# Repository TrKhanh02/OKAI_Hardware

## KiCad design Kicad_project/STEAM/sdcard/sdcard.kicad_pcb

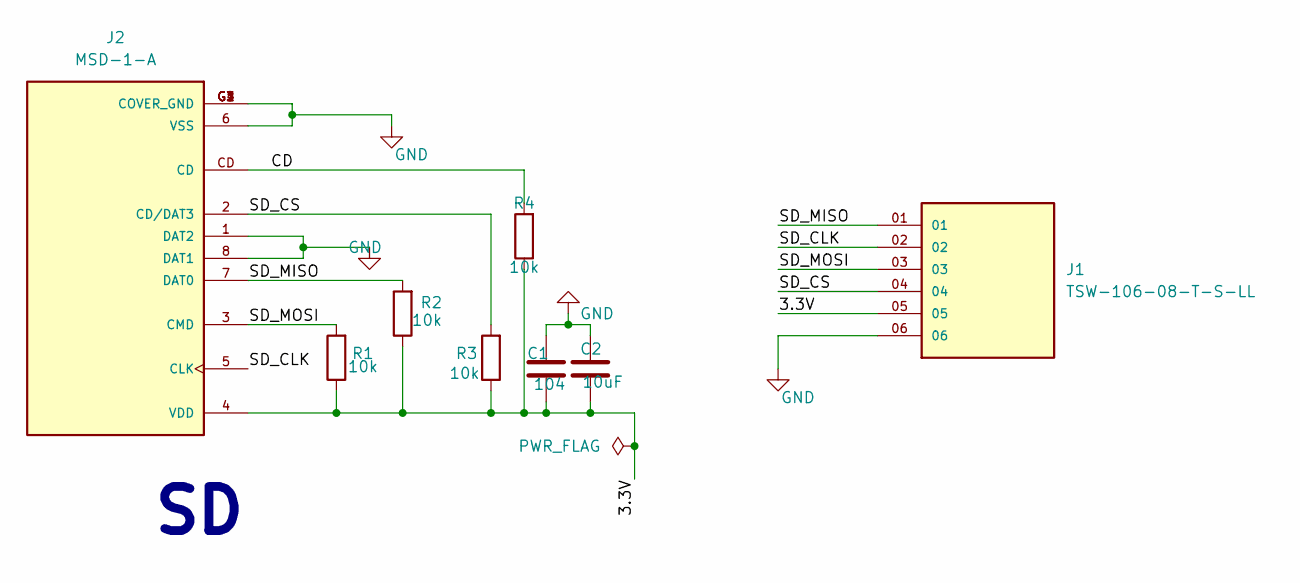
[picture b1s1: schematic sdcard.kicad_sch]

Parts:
C1: 104; C_0805_2012Metric_Pad1.18x1.45mm_HandSolder
C2: 10uF; C_0805_2012Metric_Pad1.18x1.45mm_HandSolder
J1: TSW-106-08-T-S-LL; SAMTEC_TSW-106-08-T-S-LL; PARTREV R
J2: MSD-1-A; CUI_MSD-1-A; PARTREV 1.0
R1, R2, R3, R4: 10k; R_0805_2012Metric_Pad1.20x1.40mm_HandSolder

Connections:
/3.3V: C1.1, C2.1, J1.05, J2.4 (VDD), R1.1, R2.1, R3.1, R4.1
/CD: J2.CD, R4.2
/SD_CLK: J1.02, J2.5 (CLK)
/SD_CS: J1.04, J2.2 (CD/DAT3), R3.2
/SD_MISO: J1.01, J2.7 (DAT0), R2.2
/SD_MOSI: J1.03, J2.3 (CMD), R1.2
GND: C1.2, C2.2, J1.06, J2.1 (DAT2), J2.6 (VSS), J2.8 (DAT1), J2.G1 (COVER_GND), J2.G2 (COVER_GND), J2.G3 (COVER_GND), J2.G4 (COVER_GND)

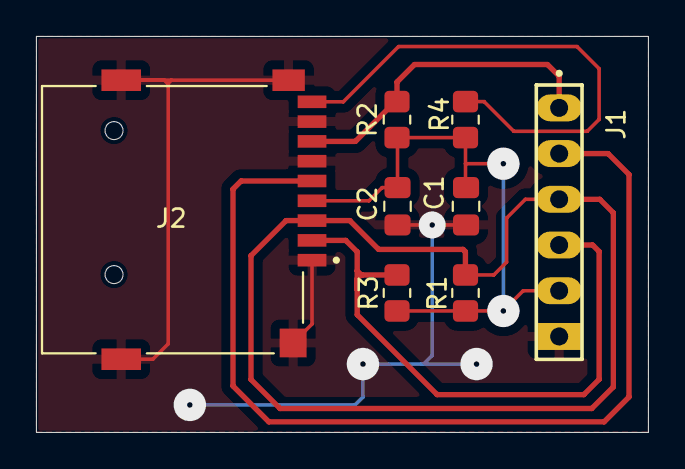
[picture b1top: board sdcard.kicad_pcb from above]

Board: 2 copper layers, 34.0 x 22.0 mm, 8 parts (0 on the bottom side), 7 nets.

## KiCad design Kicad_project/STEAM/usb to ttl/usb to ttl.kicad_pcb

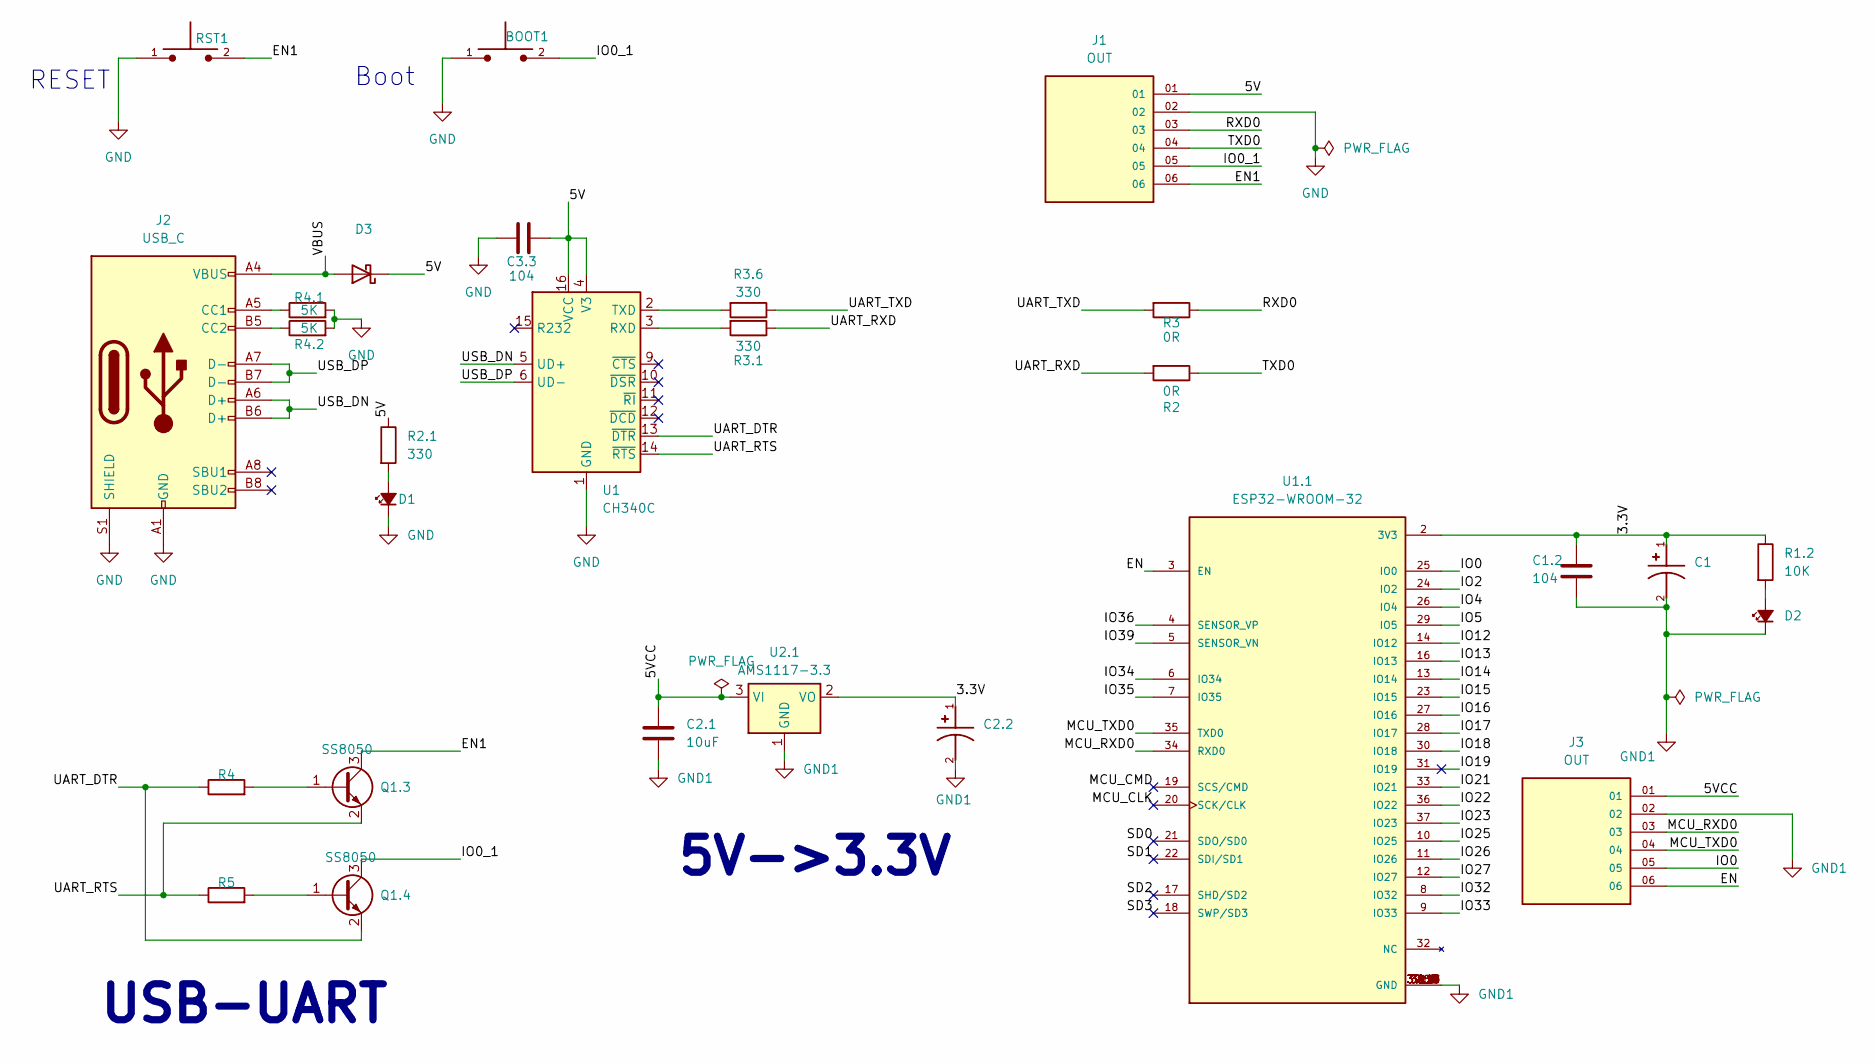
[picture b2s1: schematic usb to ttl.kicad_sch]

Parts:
BOOT1: TS10-63-26-BE-250-SMT-TR; SW_TS10-63-26-BE-250-SMT-TR; PARTREV 1.0
C1: TAJA106K016RNJ; CAPMP3216X180N; PARTREV 031320
C1.2, C3.3: 104; C_0805_2012Metric_Pad1.18x1.45mm_HandSolder
C2.1: 10uF; C_0805_2012Metric_Pad1.18x1.45mm_HandSolder
C2.2: 22uF; CAPMP3216X180N; PARTREV 031320
D1, D2: LED_Small_Filled; LED_0805_2012Metric_Pad1.15x1.40mm_HandSolder
D3: 1N5819WS; D_SOD-323_HandSoldering
J1, J3: OUT; SAMTEC_TSW-106-08-T-S-LL; PARTREV R
J2: USB_C; USB_C_Receptacle_HRO_TYPE-C-31-M-12
Q1.3, Q1.4: SS8050; SOT-23
R1.2, R4, R5: 10K; R_0805_2012Metric_Pad1.20x1.40mm_HandSolder
R2, R3: 0R; R_0805_2012Metric_Pad1.20x1.40mm_HandSolder
R2.1, R3.1, R3.6: 330; R_0805_2012Metric_Pad1.20x1.40mm_HandSolder
R4.1, R4.2: 5K; R_0805_2012Metric_Pad1.20x1.40mm_HandSolder
RST1: TS10-63-26-BE-250-SMT-TR; SW_TS10-63-26-BE-250-SMT-TR; PARTREV 1.0
U1: CH340C; SOIC-16_3.9x9.9mm_P1.27mm
U1.1: ESP32-WROOM-32; MODULE_ESP32-WROOM-32
U2.1: AMS1117-3.3; SOT-223-3_TabPin2

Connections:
/3.3V: C1.1, C1.2.1, C2.2.1, R1.2.1, U1.1.2 (3V3), U2.1.2 (VO)
/5V: C3.3.1, D3.1 (K), J1.01, R2.1.1, U1.4 (V3), U1.16 (VCC)
/5VCC: C2.1.1, J3.01, U2.1.3 (VI)
/EN: J3.06, U1.1.3 (EN)
/EN1: J1.06, Q1.3.3 (C), RST1.2
/IO0: J3.05, U1.1.25 (IO0)
/IO0_1: BOOT1.2, J1.05, Q1.4.3 (C)
/IO2: U1.1.24 (IO2)
/IO4: U1.1.26 (IO4)
/IO5: U1.1.29 (IO5)
/IO12: U1.1.14 (IO12)
/IO13: U1.1.16 (IO13)
/IO14: U1.1.13 (IO14)
/IO15: U1.1.23 (IO15)
/IO16: U1.1.27 (IO16)
/IO17: U1.1.28 (IO17)
/IO18: U1.1.30 (IO18)
/IO19: U1.1.31 (IO19)
/IO21: U1.1.33 (IO21)
/IO22: U1.1.36 (IO22)
/IO23: U1.1.37 (IO23)
/IO25: U1.1.10 (IO25)
/IO26: U1.1.11 (IO26)
/IO27: U1.1.12 (IO27)
/IO32: U1.1.8 (IO32)
/IO33: U1.1.9 (IO33)
/IO34: U1.1.6 (IO34)
/IO35: U1.1.7 (IO35)
/IO36: U1.1.4 (SENSOR_VP)
/IO39: U1.1.5 (SENSOR_VN)
/MCU_CLK: U1.1.20 (SCK/CLK)
/MCU_CMD: U1.1.19 (SCS/CMD)
/MCU_RXD0: J3.03, U1.1.34 (RXD0)
/MCU_TXD0: J3.04, U1.1.35 (TXD0)
/RXD0: J1.03, R3.1
/SD0: U1.1.21 (SDO/SD0)
/SD1: U1.1.22 (SDI/SD1)
/SD2: U1.1.17 (SHD/SD2)
/SD3: U1.1.18 (SWP/SD3)
/TXD0: J1.04, R2.1
/UART_DTR: Q1.4.2 (E), R4.1, U1.13 (~DTR)
/UART_RTS: Q1.3.2 (E), R5.1, U1.14 (~RTS)
/UART_RXD: R2.2, R3.1.1
/UART_TXD: R3.2, R3.6.1
/USB_DN: J2.A6 (D+), J2.B6 (D+), U1.5 (UD+)
/USB_DP: J2.A7 (D-), J2.B7 (D-), U1.6 (UD-)
/VBUS: D3.2 (A), J2.A4 (VBUS), J2.A9 (VBUS), J2.B4 (VBUS), J2.B9 (VBUS)
GND: BOOT1.1, C3.3.2, D1.1 (K), J1.02, J2.A1 (GND), J2.A12 (GND), J2.B1 (GND), J2.B12 (GND), J2.S1 (SHIELD), R4.1.2, R4.2.2, RST1.1, U1.1 (GND)
GND1: C1.2, C1.2.2, C2.1.2, C2.2.2, D2.1 (K), J3.02, U1.1.1 (GND), U1.1.15 (GND), U1.1.38 (GND), U1.1.39_1 (GND), U1.1.39_2 (GND), U1.1.39_3 (GND), U1.1.39_4 (GND), U1.1.39_5 (GND), U1.1.39_6 (GND), U1.1.39_7 (GND), U1.1.39_8 (GND), U1.1.39_9 (GND), U1.1.39_10 (GND), U1.1.39_11 (GND), U1.1.39_12 (GND), U1.1.39_13 (GND), U1.1.39_14 (GND), U1.1.39_15 (GND), U1.1.39_16 (GND), U1.1.39_17 (GND), U1.1.39_18 (GND), U1.1.39_19 (GND), U1.1.39_20 (GND), U1.1.39_21 (GND), U2.1.1 (GND)
unnamed: D1.2 (A), R2.1.2
unnamed: D2.2 (A), R1.2.2
unnamed: J2.A5 (CC1), R4.1.1
unnamed: J2.B5 (CC2), R4.2.1
unnamed: Q1.3.1 (B), R4.2
unnamed: Q1.4.1 (B), R5.2
unnamed: R3.1.2, U1.3 (RXD)
unnamed: R3.6.2, U1.2 (TXD)

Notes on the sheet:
USB-UART
5V->3.3V
Boot
RESET

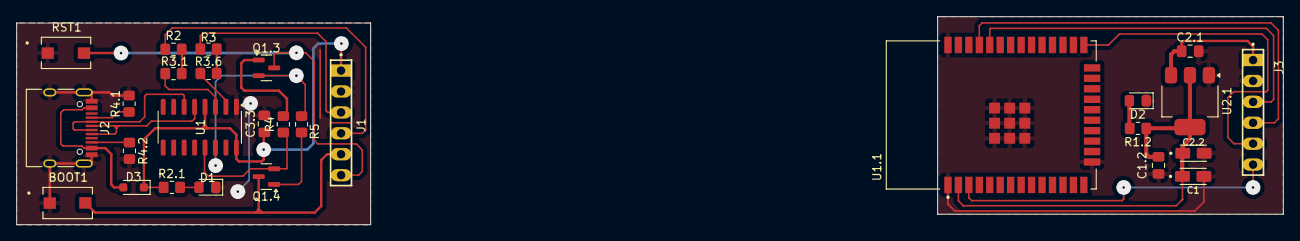
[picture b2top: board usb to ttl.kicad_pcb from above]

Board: 2 copper layers, 153.9 x 25.3 mm, 28 parts (0 on the bottom side), 28 nets.

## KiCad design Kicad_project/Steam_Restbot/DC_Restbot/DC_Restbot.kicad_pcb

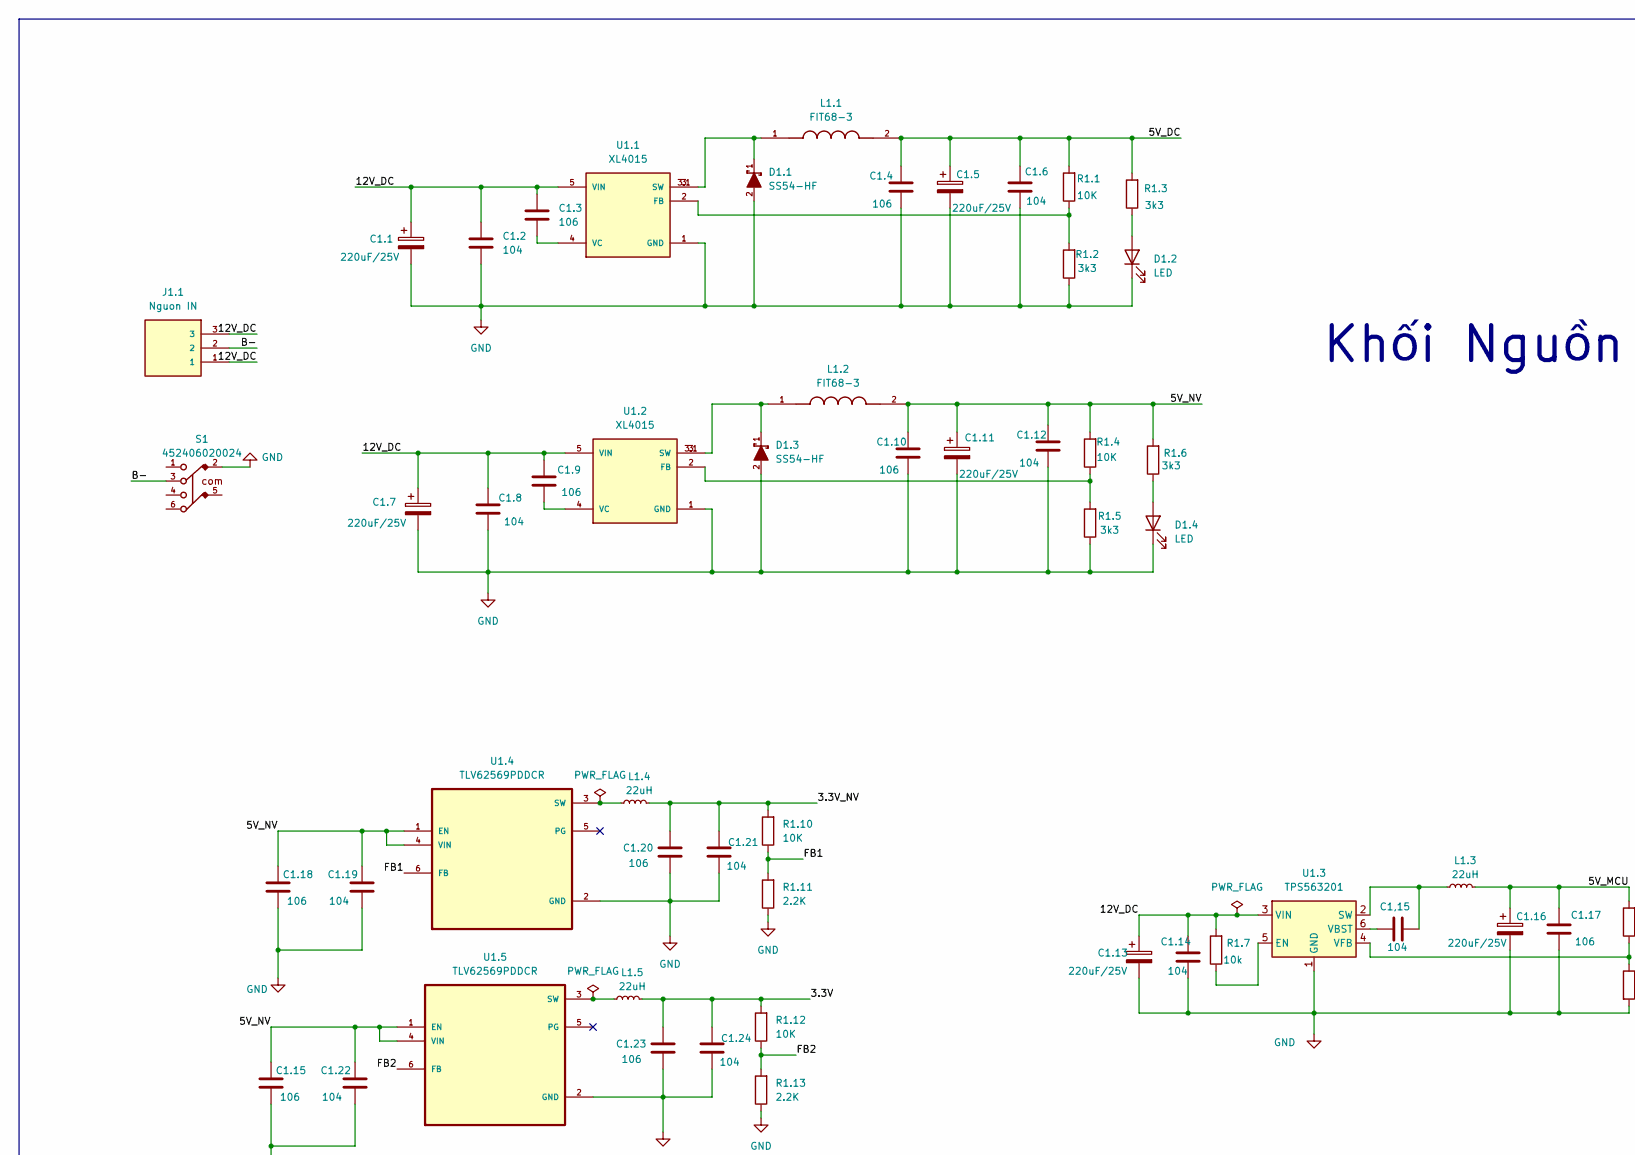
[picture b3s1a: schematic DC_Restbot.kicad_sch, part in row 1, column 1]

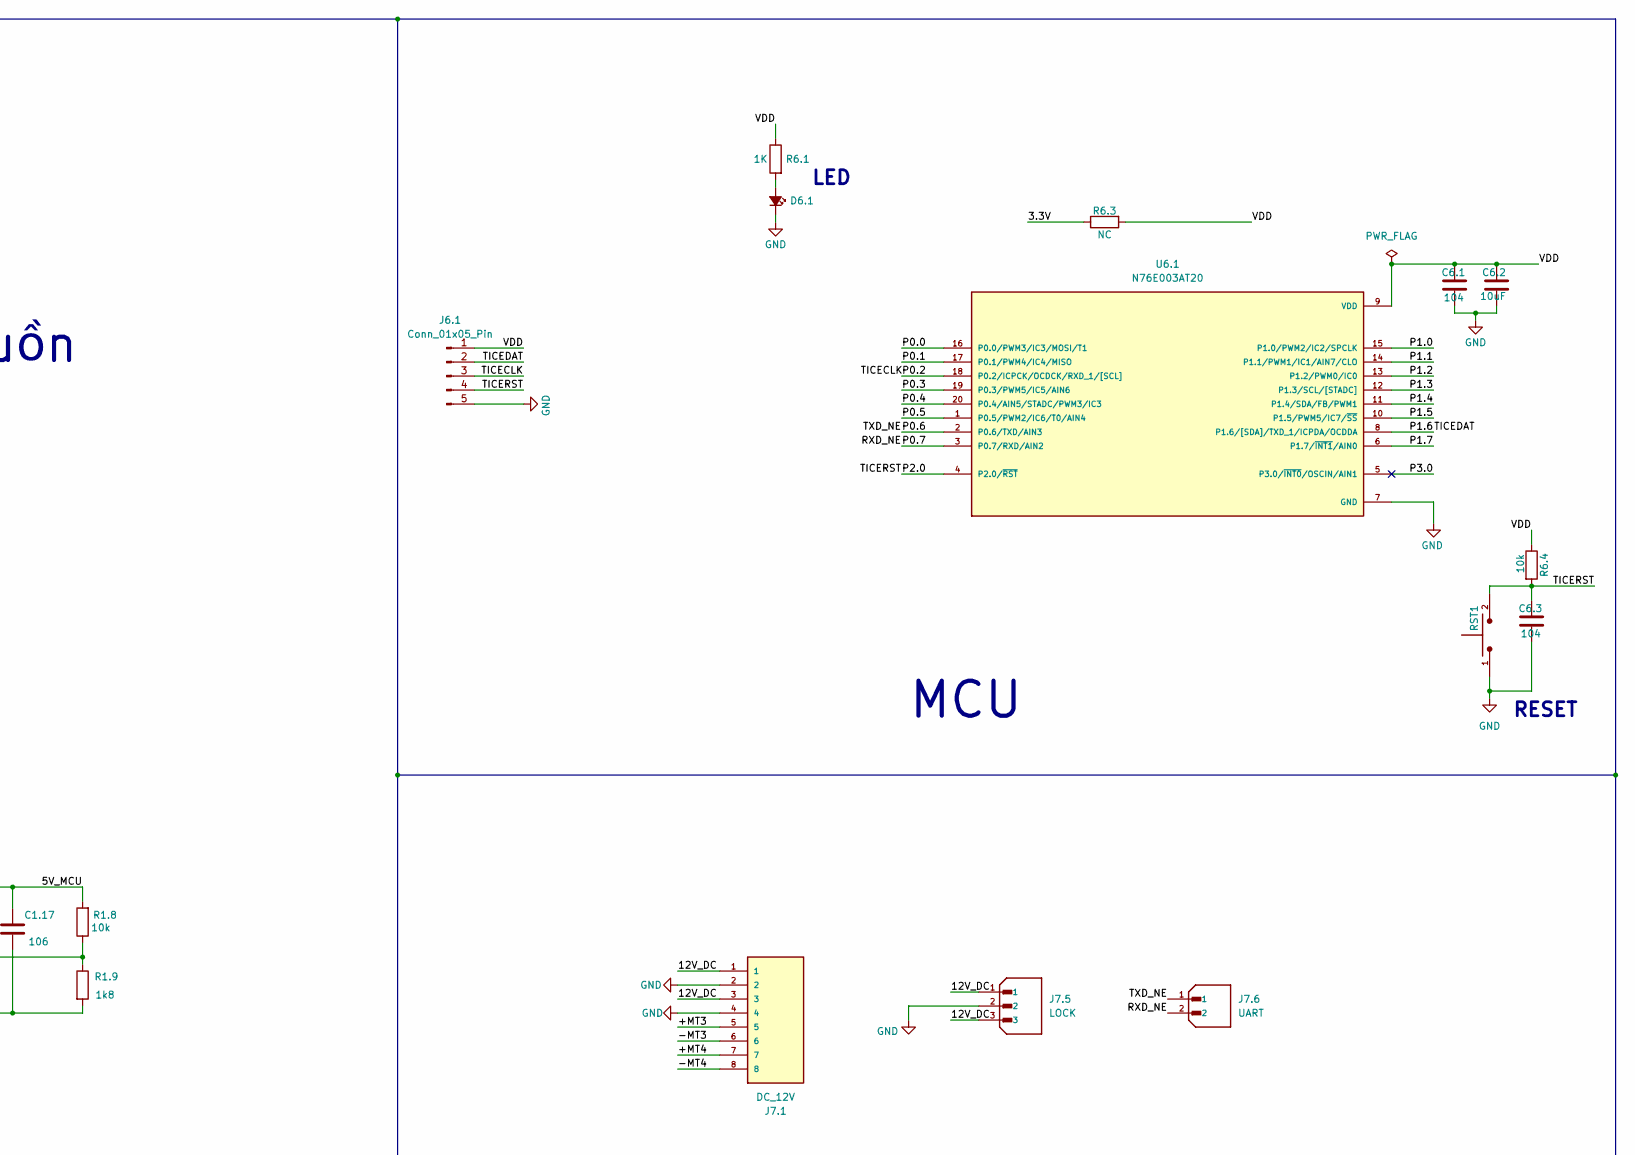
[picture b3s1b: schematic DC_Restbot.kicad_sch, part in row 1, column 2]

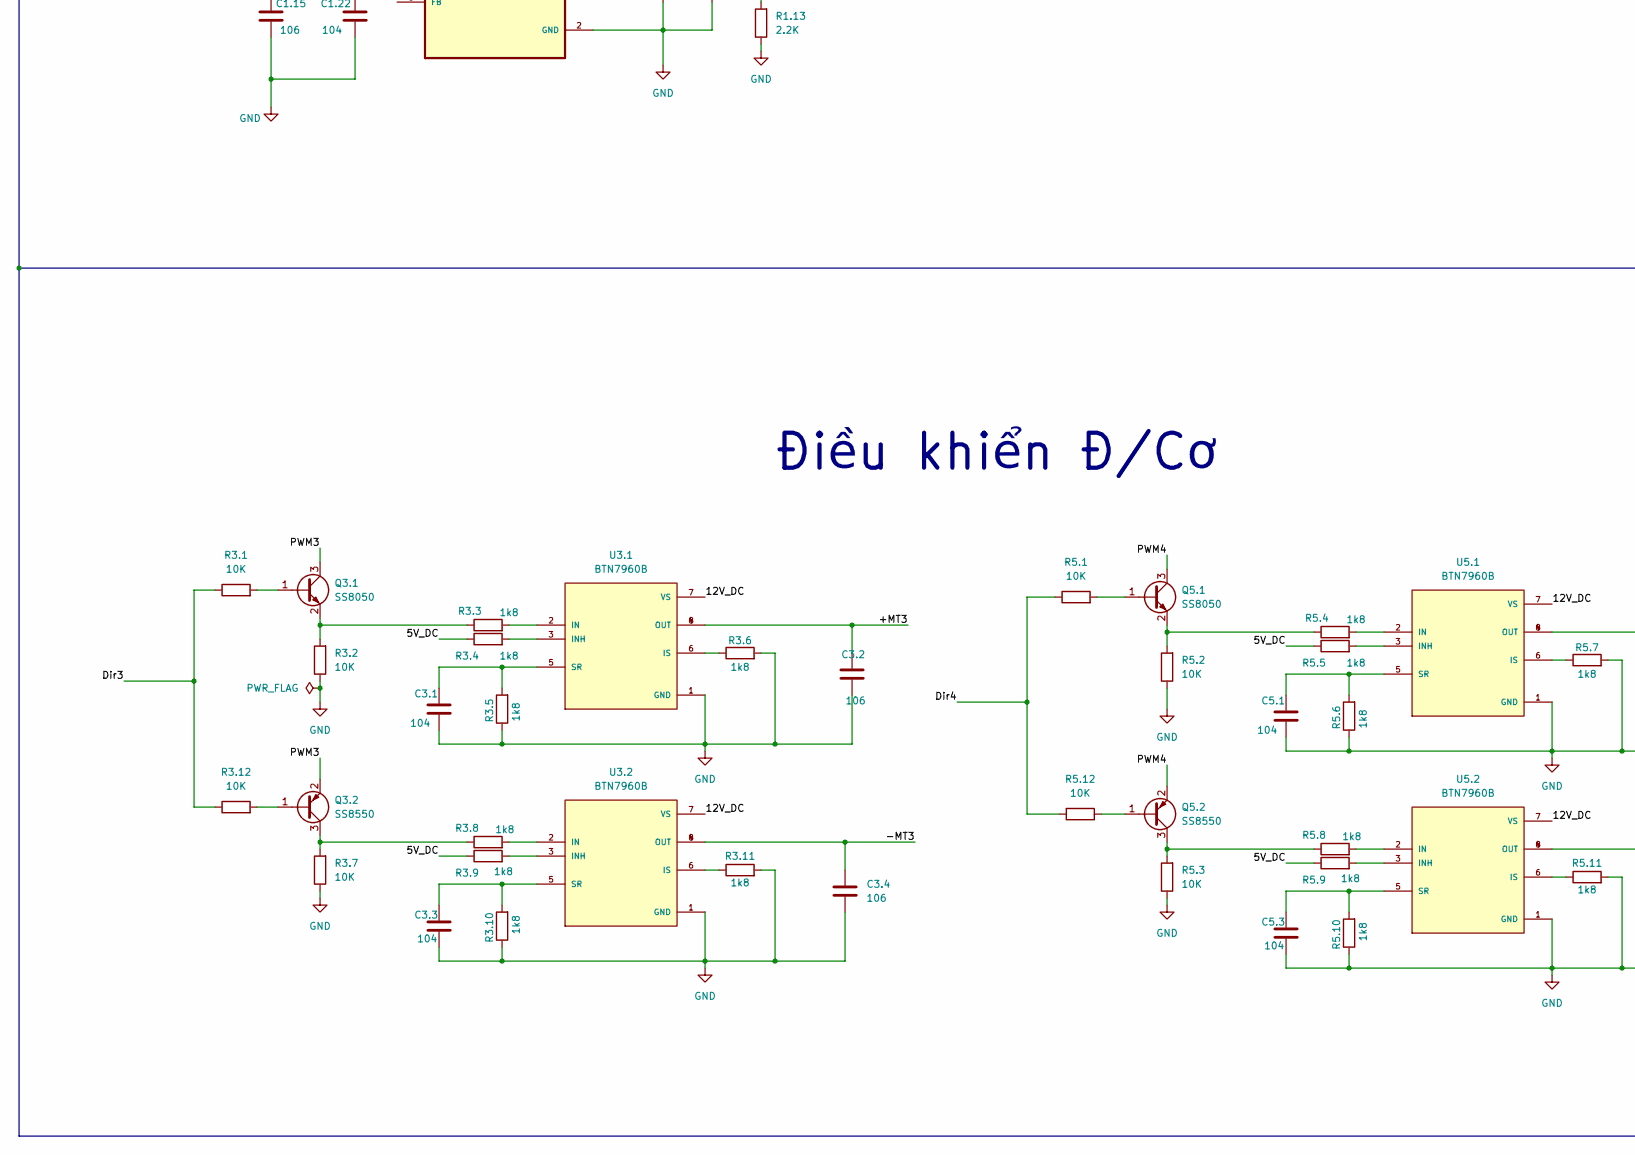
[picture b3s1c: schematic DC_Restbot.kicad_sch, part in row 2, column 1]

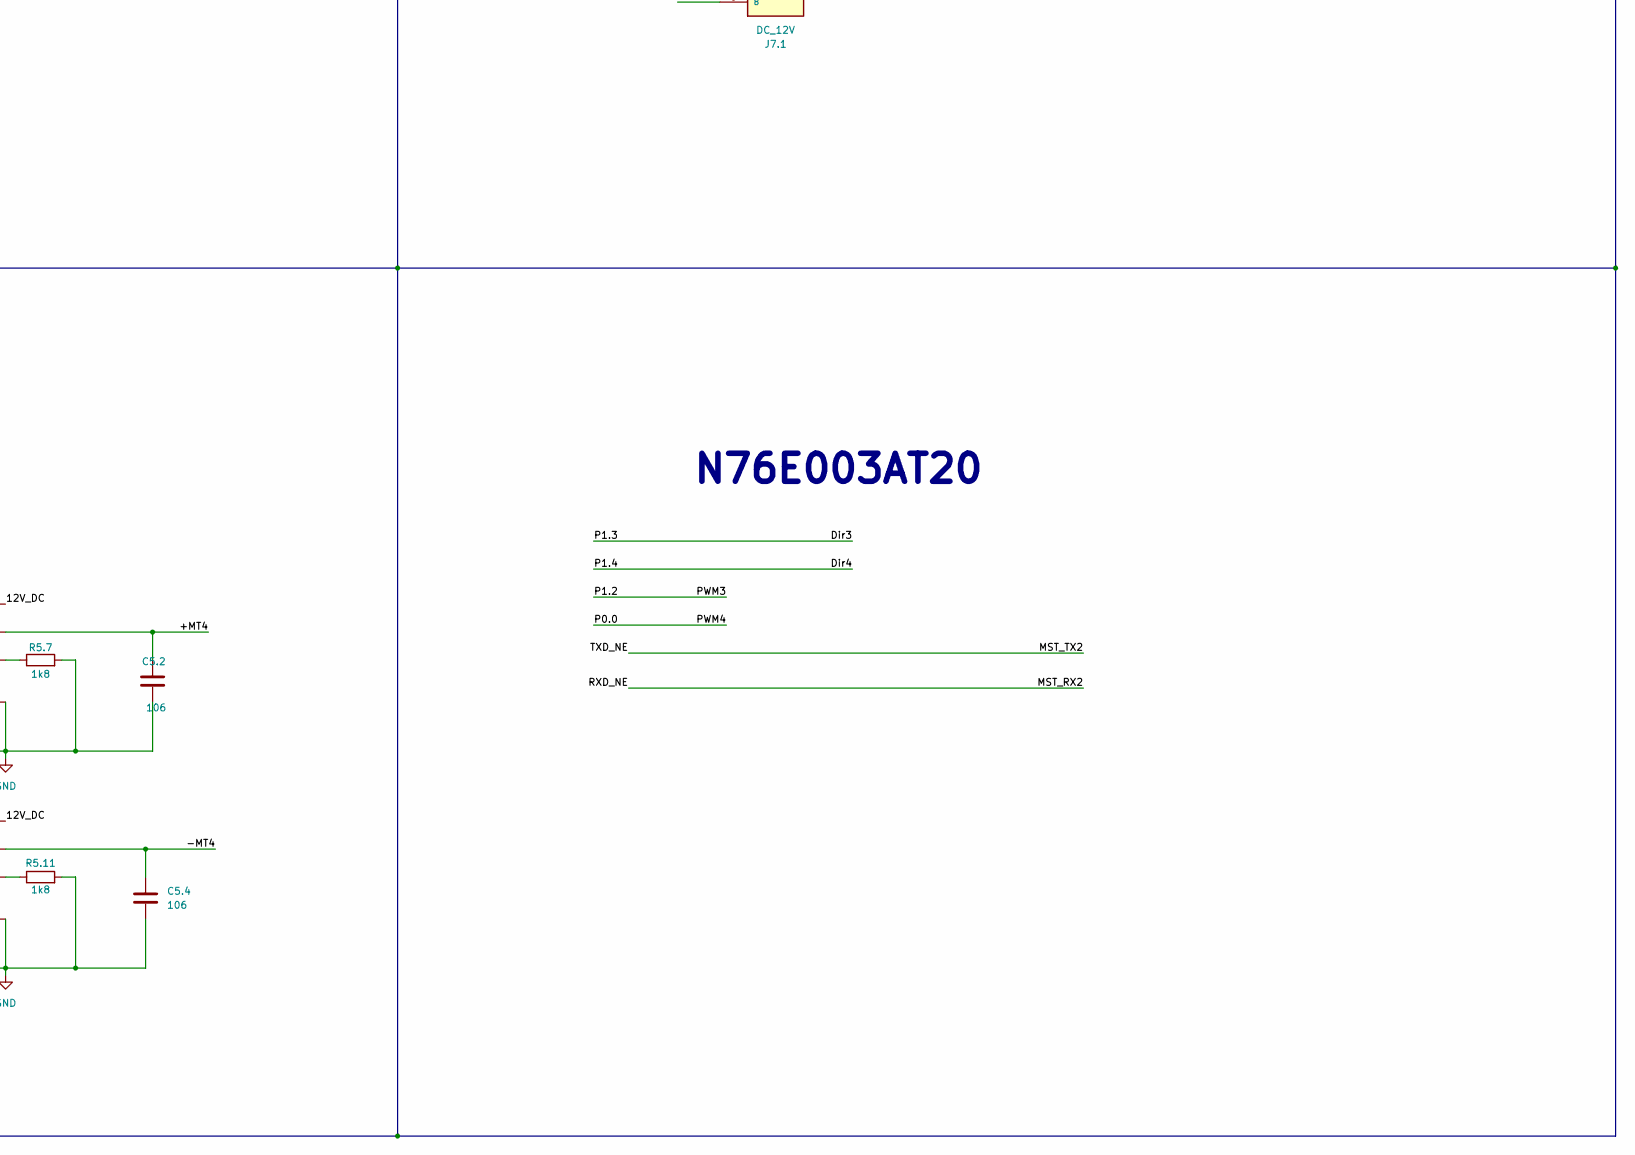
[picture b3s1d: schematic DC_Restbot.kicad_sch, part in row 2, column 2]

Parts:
C1,15, C1.2, C1.6, C1.8, C1.12, C1.14, C1.19, C1.21, C1.22, C1.24, C3.1, C3.3, C5.1, C5.3: 104; C_0805_2012Metric
C1.1, C1.5, C1.7, C1.11, C1.13, C1.16: 220uF/25V; CP_Elec_8x10.5
C1.3, C1.4, C1.9, C1.10, C1.15, C1.17, C1.18, C1.20, C1.23, C3.2, C3.4, C5.2, C5.4: 106; C_0805_2012Metric
C6.1, C6.3: 104; C_0805_2012Metric_Pad1.18x1.45mm_HandSolder
C6.2: 10uF; C_0805_2012Metric_Pad1.18x1.45mm_HandSolder
D1.1, D1.3: SS54-HF; DIOM5025X220N; MOUSER_PART_NUMBER 750-SS54-HF
D1.2, D1.4: LED; LED_0805_2012Metric
D6.1: LED_Small_Filled; LED_0805_2012Metric_Pad1.15x1.40mm_HandSolder
J1.1: Nguon IN; CUI_TBP04R1-500-03BE; PARTREV 1.0
J6.1: Conn_01x05_Pin; PinHeader_1x05_P2.54mm_Vertical
J7.1: DC_12V; CUI_TBP04R1-500-08BE; PARTREV 1.0
J7.5: LOCK; JST_B3B-XH-A; PARTREV 7/4/21
J7.6: UART; JST_B2B-XH-A_LF__SN_; PARTREV N/A
L1.1, L1.2: FIT68-3; IND_FIT68-3; PARTREV N/A
L1.3, L1.4, L1.5: 22uH; L_Ferrocore_DLG-0705
Q3.1, Q5.1: SS8050; SOT-23
Q3.2, Q5.2: SS8550; SOT-23
R1.1, R1.4, R1.10, R1.12: 10K; R_0805_2012Metric
R1.2, R1.3, R1.5, R1.6: 3k3; R_0805_2012Metric
R1.7, R1.8: 10k; R_0805_2012Metric
R1.9, R3.3, R3.4, R3.5, R3.6, R3.8, R3.9, R3.10, R3.11, R5.4, R5.5, R5.6, R5.7, R5.8, R5.9, R5.10, R5.11: 1k8; R_0805_2012Metric
R1.11, R1.13: 2.2K; R_0805_2012Metric
R3.1, R3.2, R3.7, R3.12, R5.1, R5.2, R5.3, R5.12: 10K; R_0805_2012Metric_Pad1.20x1.40mm_HandSolder
R6.1: 1K; R_0805_2012Metric_Pad1.20x1.40mm_HandSolder
R6.3: NC; R_0805_2012Metric_Pad1.20x1.40mm_HandSolder
R6.4: 10k; R_0805_2012Metric_Pad1.20x1.40mm_HandSolder
RST1: TS10-63-26-BE-250-SMT-TR; SW_TS10-63-26-BE-250-SMT-TR; PARTREV 1.0
S1: 452406020024
U1.1, U1.2: XL4015; CONV_XL4015; PARTREV 1.5
U1.3: TPS563201; SOT-23-6
U1.4, U1.5: TLV62569PDDCR; SOT95P280X110-6N
U3.1, U3.2, U5.1, U5.2: BTN7960B; DPAK127P1490X440-8N; PARTREV 1.1
U6.1: N76E003AT20; SOP65P640X120-20N; PARTREV 1.04

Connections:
/3.3V: C1.23.1, C1.24.1, L1.5.1, R1.12.2, R6.3.1
/3.3V_NV: C1.20.1, C1.21.1, L1.4.1, R1.10.2
/5V_DC: C1.4.1, C1.5.1, C1.6.1, L1.1.2, R1.1.2, R1.3.2, R3.4.1, R3.9.1, R5.5.1, R5.9.1
/5V_MCU: C1.16.1, C1.17.1, L1.3.1, R1.8.2
/5V_NV: C1.10.1, C1.11.1, C1.12.1, C1.15.1, C1.18.1, C1.19.1, C1.22.1, L1.2.2, R1.4.2, R1.6.2, U1.4.1 (EN), U1.4.4 (VIN), U1.5.1 (EN), U1.5.4 (VIN)
/12V_DC: C1.1.1, C1.2.1, C1.3.1, C1.7.1, C1.8.1, C1.9.1, C1.13.1, C1.14.1, J1.1.1, J1.1.3, J7.1.1, J7.1.3, J7.5.1, J7.5.3, R1.7.2, U1.1.5 (VIN), U1.2.5 (VIN), U1.3.3 (VIN), U3.1.7 (VS), U3.2.7 (VS), U5.1.7 (VS), U5.2.7 (VS)
/+MT3: C3.2.2, J7.1.5, U3.1.4 (OUT), U3.1.8 (OUT)
/+MT4: C5.2.2, J7.1.7, U5.1.4 (OUT), U5.1.8 (OUT)
/-MT3: C3.4.2, J7.1.6, U3.2.4 (OUT), U3.2.8 (OUT)
/-MT4: C5.4.2, J7.1.8, U5.2.4 (OUT), U5.2.8 (OUT)
/B-: J1.1.2, S1.3
/Dir3: R3.1.1, R3.12.1, U6.1.12 (P1.3/SCL/[STADC])
/Dir4: R5.1.1, R5.12.1, U6.1.11 (P1.4/SDA/FB/PWM1)
/FB1: R1.10.1, R1.11.2, U1.4.6 (FB)
/FB2: R1.12.1, R1.13.2, U1.5.6 (FB)
/MST_RX2: J7.6.2, U6.1.3 (P0.7/RXD/AIN2)
/MST_TX2: J7.6.1, U6.1.2 (P0.6/TXD/AIN3)
/P0.0: Q5.1.3 (C), Q5.2.2 (E), U6.1.16 (P0.0/PWM3/IC3/MOSI/T1)
/P0.1: U6.1.17 (P0.1/PWM4/IC4/MISO)
/P0.2: J6.1.3, U6.1.18 (P0.2/ICPCK/OCDCK/RXD_1/[SCL])
/P0.3: U6.1.19 (P0.3/PWM5/IC5/AIN6)
/P0.4: U6.1.20 (P0.4/AIN5/STADC/PWM3/IC3)
/P0.5: U6.1.1 (P0.5/PWM2/IC6/T0/AIN4)
/P1.0: U6.1.15 (P1.0/PWM2/IC2/SPCLK)
/P1.1: U6.1.14 (P1.1/PWM1/IC1/AIN7/CLO)
/P1.2: Q3.1.3 (C), Q3.2.2 (E), U6.1.13 (P1.2/PWM0/IC0)
/P1.5: U6.1.10 (P1.5/PWM5/IC7/~SS)
/P1.6: J6.1.2, U6.1.8 (P1.6/[SDA]/TXD_1/ICPDA/OCDDA)
/P1.7: U6.1.6 (P1.7/~INT1/AIN0)
/P2.0: C6.3.1, J6.1.4, R6.4.2, RST1.2, U6.1.4 (P2.0/~RST)
/P3.0: U6.1.5 (P3.0/~INT0/OSCIN/AIN1)
/VDD: C6.1.1, C6.2.1, J6.1.1, R6.1.1, R6.3.2, R6.4.1, U6.1.9 (VDD)
GND: C1.1.2, C1.2.2, C1.4.2, C1.5.2, C1.6.2, C1.7.2, C1.8.2, C1.10.2, C1.11.2, C1.12.2, C1.13.2, C1.14.2, C1.15.2, C1.16.2, C1.17.2, C1.18.2, C1.19.2, C1.20.2, C1.21.2, C1.22.2, C1.23.2, C1.24.2, C3.1.1, C3.2.1, C3.3.1, C3.4.1, C5.1.1, C5.2.1, C5.3.1, C5.4.1, C6.1.2, C6.2.2, C6.3.2, D1.1.2, D1.2.1 (K), D1.3.2, D1.4.1 (K), D6.1.1 (K), J6.1.5, J7.1.2, J7.1.4, J7.5.2, R1.2.1, R1.5.1, R1.9.2, R1.11.1, R1.13.1, R3.2.1, R3.5.1, R3.6.2, R3.7.1, R3.10.1, R3.11.2, R5.2.1, R5.3.1, R5.6.1, R5.7.2, R5.10.1, R5.11.2, RST1.1, S1.2, U1.1.1 (GND), U1.2.1 (GND), U1.3.1 (GND), U1.4.2 (GND), U1.5.2 (GND), U3.1.1 (GND), U3.2.1 (GND), U5.1.1 (GND), U5.2.1 (GND), U6.1.7 (GND)
unnamed: D1.1.1, L1.1.1, U1.1.3 (SW), U1.1.3.1 (SW)
unnamed: D1.2.2 (A), R1.3.1
unnamed: D1.3.1, L1.2.1, U1.2.3 (SW), U1.2.3.1 (SW)
unnamed: D1.4.2 (A), R1.6.1
unnamed: D6.1.2 (A), R6.1.2
unnamed: Q3.1.1 (B), R3.1.2
unnamed: Q3.1.2 (E), R3.2.2, R3.3.1
unnamed: Q3.2.1 (B), R3.12.2
unnamed: Q3.2.3 (C), R3.7.2, R3.8.1
unnamed: Q5.1.1 (B), R5.1.2
unnamed: Q5.1.2 (E), R5.2.2, R5.4.1
unnamed: Q5.2.1 (B), R5.12.2
unnamed: Q5.2.3 (C), R5.3.2, R5.8.1
unnamed: R1.1.1, R1.2.2, U1.1.2 (FB)
unnamed: C1.3.2, U1.1.4 (VC)
unnamed: R1.4.1, R1.5.2, U1.2.2 (FB)
unnamed: C1.9.2, U1.2.4 (VC)
unnamed: R1.7.1, U1.3.5 (EN)
unnamed: C1,15.2, L1.3.2, U1.3.2 (SW)
unnamed: C1,15.1, U1.3.6 (VBST)
unnamed: R1.8.1, R1.9.1, U1.3.4 (VFB)
unnamed: L1.4.2, U1.4.3 (SW)
unnamed: L1.5.2, U1.5.3 (SW)
unnamed: R3.3.2, U3.1.2 (IN)
unnamed: R3.4.2, U3.1.3 (INH)
unnamed: R3.6.1, U3.1.6 (IS)
unnamed: C3.1.2, R3.5.2, U3.1.5 (SR)
unnamed: R3.8.2, U3.2.2 (IN)
unnamed: R3.9.2, U3.2.3 (INH)
unnamed: R3.11.1, U3.2.6 (IS)
unnamed: C3.3.2, R3.10.2, U3.2.5 (SR)
unnamed: R5.4.2, U5.1.2 (IN)
unnamed: R5.5.2, U5.1.3 (INH)
unnamed: R5.7.1, U5.1.6 (IS)
unnamed: C5.1.2, R5.6.2, U5.1.5 (SR)
unnamed: R5.8.2, U5.2.2 (IN)
unnamed: R5.9.2, U5.2.3 (INH)
unnamed: R5.11.1, U5.2.6 (IS)
unnamed: C5.3.2, R5.10.2, U5.2.5 (SR)

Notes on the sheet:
MCU
Khối Nguồn
LED
N76E003AT20
RESET
Điều khiển Đ/Cơ

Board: 2 copper layers, 107 parts (0 on the bottom side), 63 nets, no tracks yet.

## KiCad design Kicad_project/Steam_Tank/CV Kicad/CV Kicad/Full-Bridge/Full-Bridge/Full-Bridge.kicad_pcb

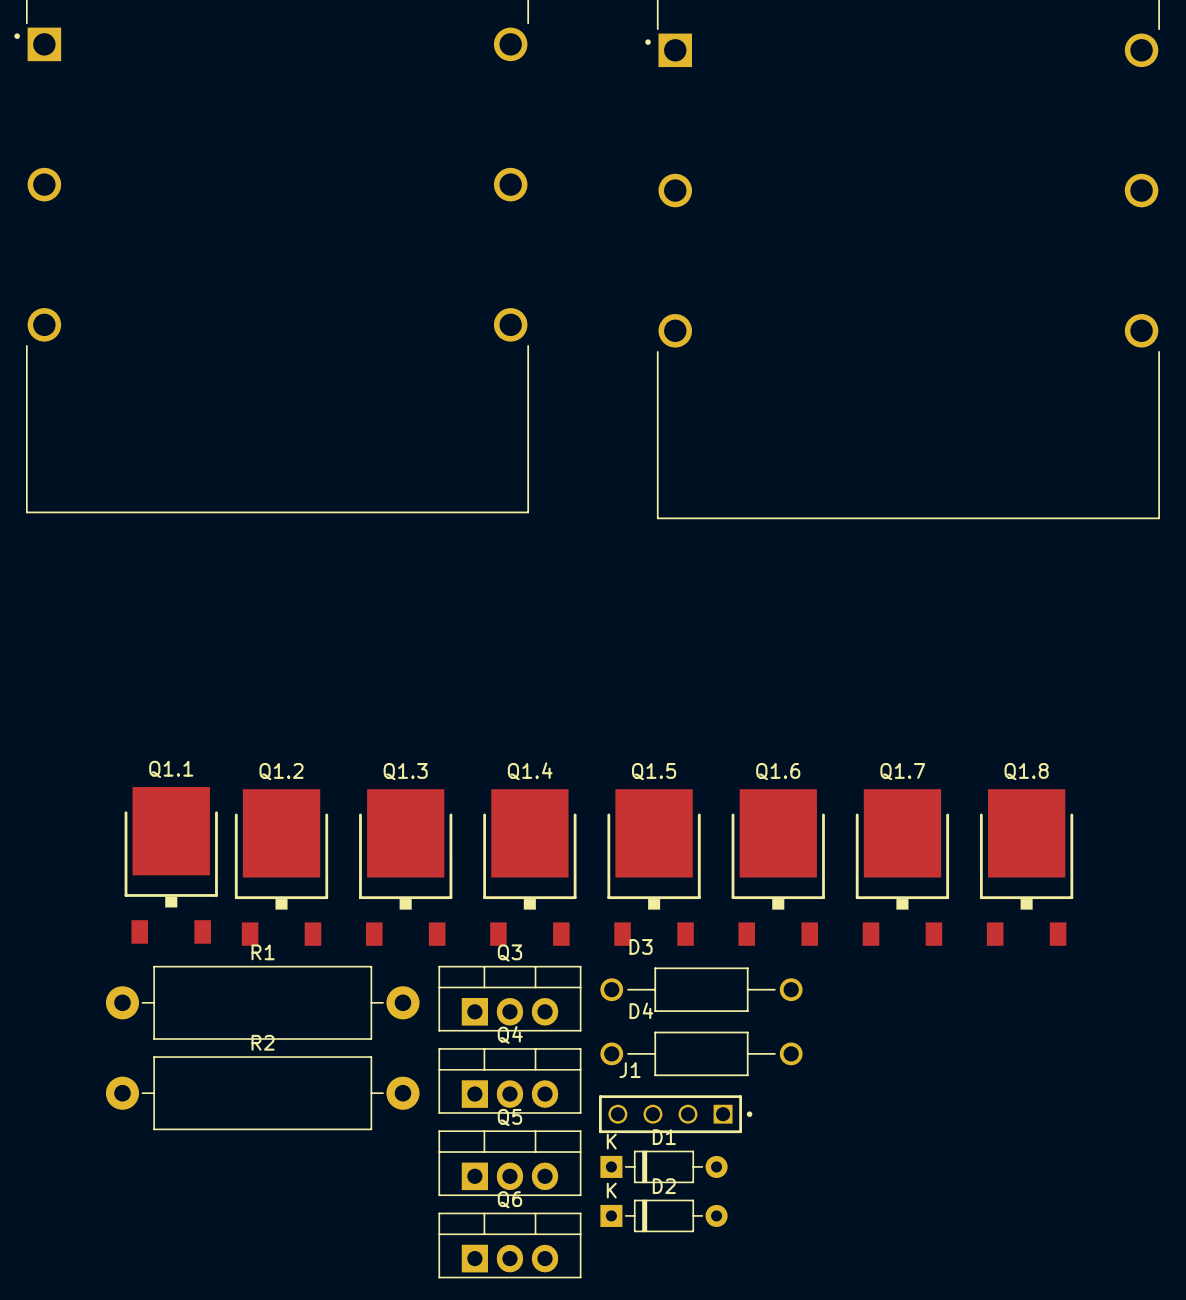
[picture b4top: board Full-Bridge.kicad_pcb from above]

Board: 2 copper layers, 21 parts (0 on the bottom side), 18 nets, no tracks yet.

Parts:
D1, D2: 1N4148; D_DO-35_SOD27_P7.62mm_Horizontal
D3, D4: P6KE12CA; DIOAD1300W80L670D310
J1: MTSW-104-12-T-S-740; SAMTEC_MTSW-104-12-T-S-740
Q1.1, Q1.2, Q1.5, Q1.7: D882; TO-252
Q1.3, Q1.4, Q1.6, Q1.8: B772; TO-252
Q3, Q4, Q5, Q6: IPP060N06N; TO-220-3_Vertical
R1, R2: 4,7R; R_Axial_DIN0516_L15.5mm_D5.0mm_P20.32mm_Horizontal
T1, T2: PC-56-180; XFMR_PC-56-180

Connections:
+10V: Q1.1.3, Q1.2.3, Q1.5.3, Q1.7.3
/PWM1: J1.01, Q1.1.1, Q1.3.1
/PWM2: J1.02, Q1.2.1, Q1.4.1
/PWM3: J1.03, Q1.5.1, Q1.6.1
/PWM4: J1.04, Q1.7.1, Q1.8.1
GND1: Q1.3.3, Q1.4.3, Q1.6.3, Q1.8.3
unnamed: D1.2 (A), D3.1, R1.1
unnamed: D1.1 (K), R1.2
unnamed: D2.2 (A), D4.1, R2.1
unnamed: D2.1 (K), R2.2
unnamed: Q1.1.2, Q1.3.2, T1.1
unnamed: Q1.2.2, Q1.4.2, T1.2
unnamed: Q1.5.2, Q1.6.2, T2.1
unnamed: Q1.7.2, Q1.8.2, T2.2
unnamed: Q3.2 (D), Q5.2 (D)
unnamed: Q3.3 (S), Q4.2 (D)
unnamed: Q4.3 (S), Q6.3 (S)
unnamed: Q5.3 (S), Q6.2 (D)

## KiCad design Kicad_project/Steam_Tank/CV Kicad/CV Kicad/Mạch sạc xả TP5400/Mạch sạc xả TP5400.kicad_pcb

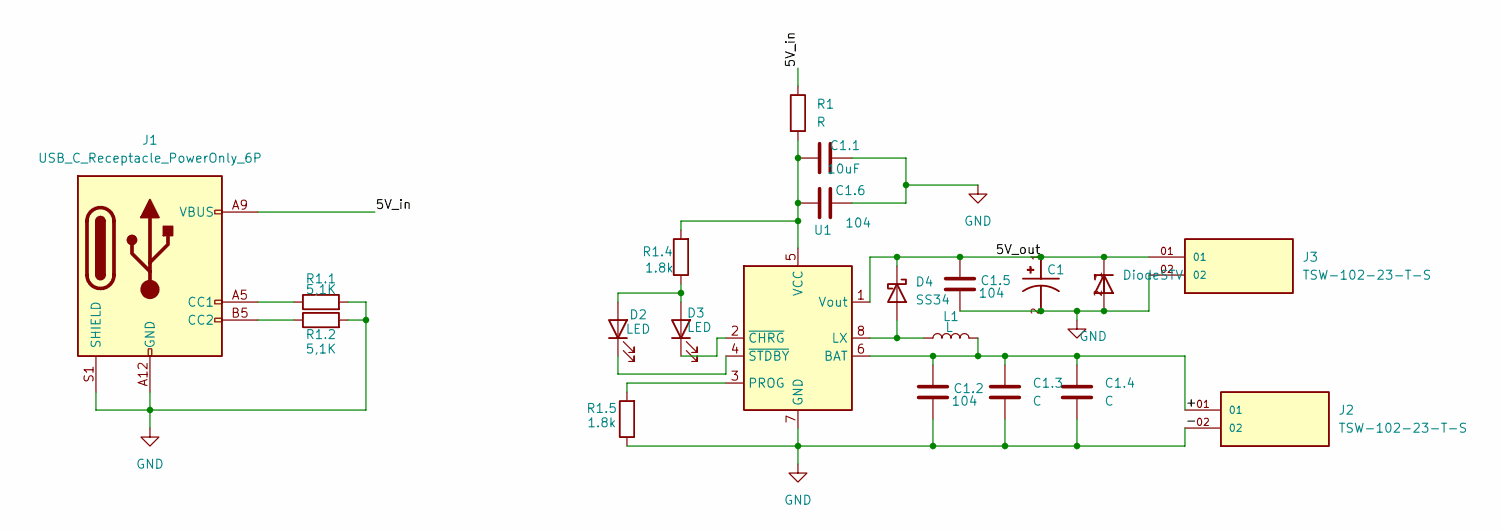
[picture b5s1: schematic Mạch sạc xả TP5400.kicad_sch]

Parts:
C1: TAJA106K016RNJ; CAPMP3216X180N; PARTREV 031320
C1.1: 10uF; C_0805_2012Metric_Pad1.18x1.45mm_HandSolder
C1.2, C1.5, C1.6: 104; C_0805_2012Metric_Pad1.18x1.45mm_HandSolder
C1.3, C1.4: C; C_1206_3216Metric
D2, D3: LED; LED_0805_2012Metric_Pad1.15x1.40mm_HandSolder
D4: SS34; D_SMA
DiodeSTV: SMBJ28A-13-F; DIOM5336X250N; PARTREV 20 - 2
J1: USB_C_Receptacle_PowerOnly_6P; USB_C_Receptacle_GCT_USB4125-xx-x_6P_TopMnt_Horizontal
J2, J3: TSW-102-23-T-S; SAMTEC_TSW-102-23-T-S; PARTREV R
L1: L; L_10.4x10.4_H4.8
R1: R; R_2512_6332Metric
R1.1, R1.2: 5,1K; R_0805_2012Metric_Pad1.20x1.40mm_HandSolder
R1.4, R1.5: 1.8k; R_0805_2012Metric_Pad1.20x1.40mm_HandSolder
U1: TP4056-42-ESOP8; SOIC-8-1EP_3.9x4.9mm_P1.27mm_EP2.41x3.3mm

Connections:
/5V_in: J1.A9 (VBUS), J1.B9 (VBUS), R1.1
/5V_out: C1.1, C1.5.1, D4.1 (K), DiodeSTV.1, J3.01, U1.1 (Vout); also elsewhere on the board
/+: C1.2.1, C1.3.1, C1.4.1, J2.01, L1.2, U1.6 (BAT)
GND: C1.2, C1.1.2, C1.2.2, C1.3.2, C1.4.2, C1.5.2, C1.6.2, DiodeSTV.2, J1.A12 (GND), J1.B12 (GND), J1.S1 (SHIELD), J2.02, J3.02, R1.1.2, R1.2.2, R1.5.1, U1.7 (GND), U1.9; also elsewhere on the board
unnamed: D2.2 (A), D3.2 (A), R1.4.1
unnamed: D2.1 (K), U1.4 (~STDBY)
unnamed: D3.1 (K), U1.2 (~CHRG)
unnamed: D4.2 (A), L1.1, U1.8 (LX)
unnamed: J1.A5 (CC1), R1.1.1
unnamed: J1.B5 (CC2), R1.2.1
unnamed: R1.5.2, U1.3 (PROG)
unnamed: C1.1.1, C1.6.1, R1.2, R1.4.2, U1.5 (VCC)

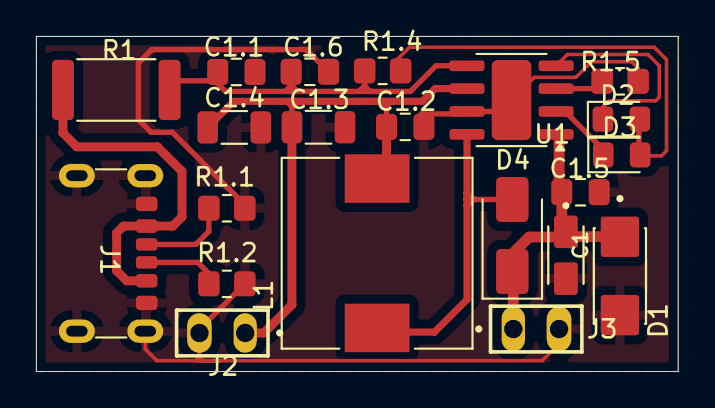
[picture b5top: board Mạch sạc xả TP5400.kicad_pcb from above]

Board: 2 copper layers, 35.7 x 18.6 mm, 21 parts (0 on the bottom side), 12 nets.

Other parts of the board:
D1: SMBJ28A-13-F; DIOM5336X250N

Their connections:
/5V_out: D1.1; also elsewhere on the board
GND: D1.2; also elsewhere on the board
